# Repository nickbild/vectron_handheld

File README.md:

# Vectron Handheld

Vectron Handheld is a retro handheld gaming console based on the [6502 CPU](https://en.wikipedia.org/wiki/MOS_Technology_6502).  It has five input buttons (up, down, left, right, fire) and a 1.8" 128x160 18-bit color TFT LCD display.  

I have developed an [implementation of Pong](https://github.com/nickbild/vectron_handheld/blob/master/game.asm) to demonstrate Vectron Handheld's capabilities.

## How It Works

The KiCad design files are [available here](https://github.com/nickbild/vectron_handheld/tree/master/vectron_handheld_pcb).

The W65C02 is clocked at 8MHz.  The console has 32KB of RAM, and 32KB of ROM is available to store the game.  A few 7400-series logic chips are used for address decoding and button debouncing.  All components are through-hole, and aside from the modern display, the components are contemporaries of the original 6502 processor.

A W65C22 VIA is used to extend the number of interrupts available to the CPU for capturing button presses.  The VIA is also used to bit bang the SPI TFT LCD display interface.  My implementation of [Pong](https://github.com/nickbild/vectron_handheld/blob/master/game.asm) demonstrates how to use the buttons and the display in a game.

A 273 mm x 221 mm 4-layer PCB was designed in KiCad.  There is definitely opportunity to reduce the size of the board with a tighter layout if a smaller device is desired (this was my first crack at designing a PCB).

The Vectron Handheld runs at 5V and draws ~150 mA of current.

## Media

YouTube:  
https://www.youtube.com/watch?v=bRN5SaRVa04

Vectron Handheld:

Close-up:

The breadboard prototype from which the PCB was designed:

Playing Pong:

Unpopulated PCB:

## Bill of Materials

- 1	x W65C02
- 1	x W65C22
- 1	x 8MHz Crystal
- 1	x SN74HC32N
- 1	x SN74HC08N
- 1	x SN74LS04N
- 2	x 74LS682
- 1	x SN74HC14N
- 1	x AS6C62256A-70PCN
- 1	x AT28C256-15PU
- 6 x pushbutton
- 9	x 10K resistor
- 8	x 3.3K resistor
- 1	x 1.8" 128x160 18-bit color TFT LCD display
- 1	x 220uF capacitor
- 5	x 1,000 pF capacitor
- 2 x 40 pin DIP IC socket
- 2 x 28 pin DIP IC socket

## Also See

Check out some of my other 6502-based projects:

- [Vectron 64 breadboard computer](https://github.com/nickbild/vectron_64)  
- [6502 virtual reality headset](https://github.com/nickbild/vectron_vr)  
- [Play Atari 2600 games with gestures](https://github.com/nickbild/vectron_ai)

## About the Author

[Nick A. Bild, MS](https://nickbild79.firebaseapp.com/#!/)

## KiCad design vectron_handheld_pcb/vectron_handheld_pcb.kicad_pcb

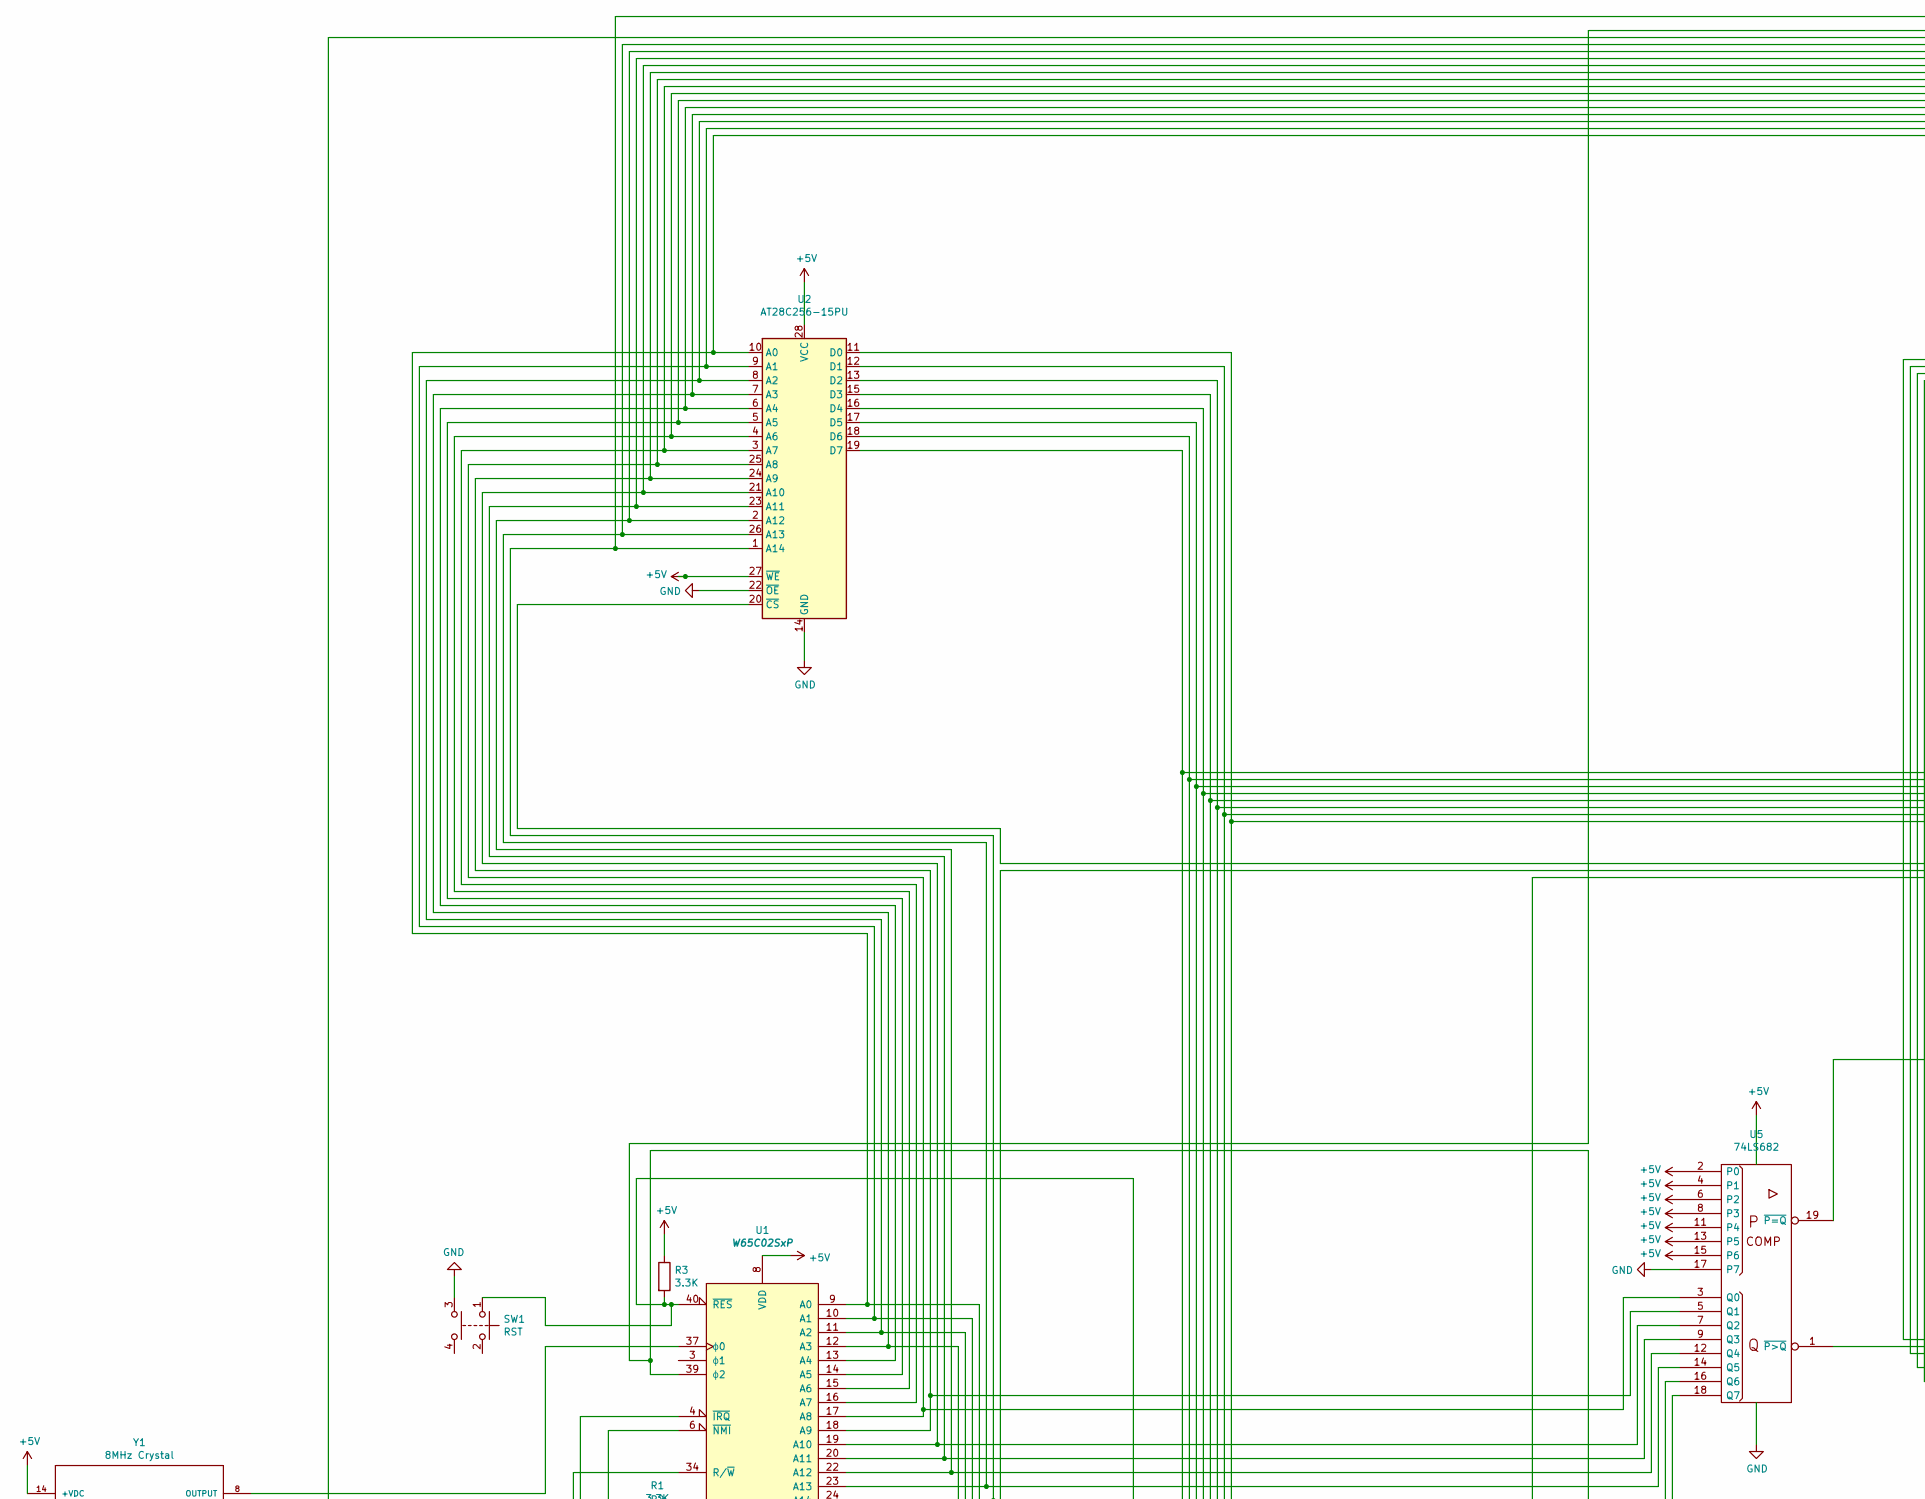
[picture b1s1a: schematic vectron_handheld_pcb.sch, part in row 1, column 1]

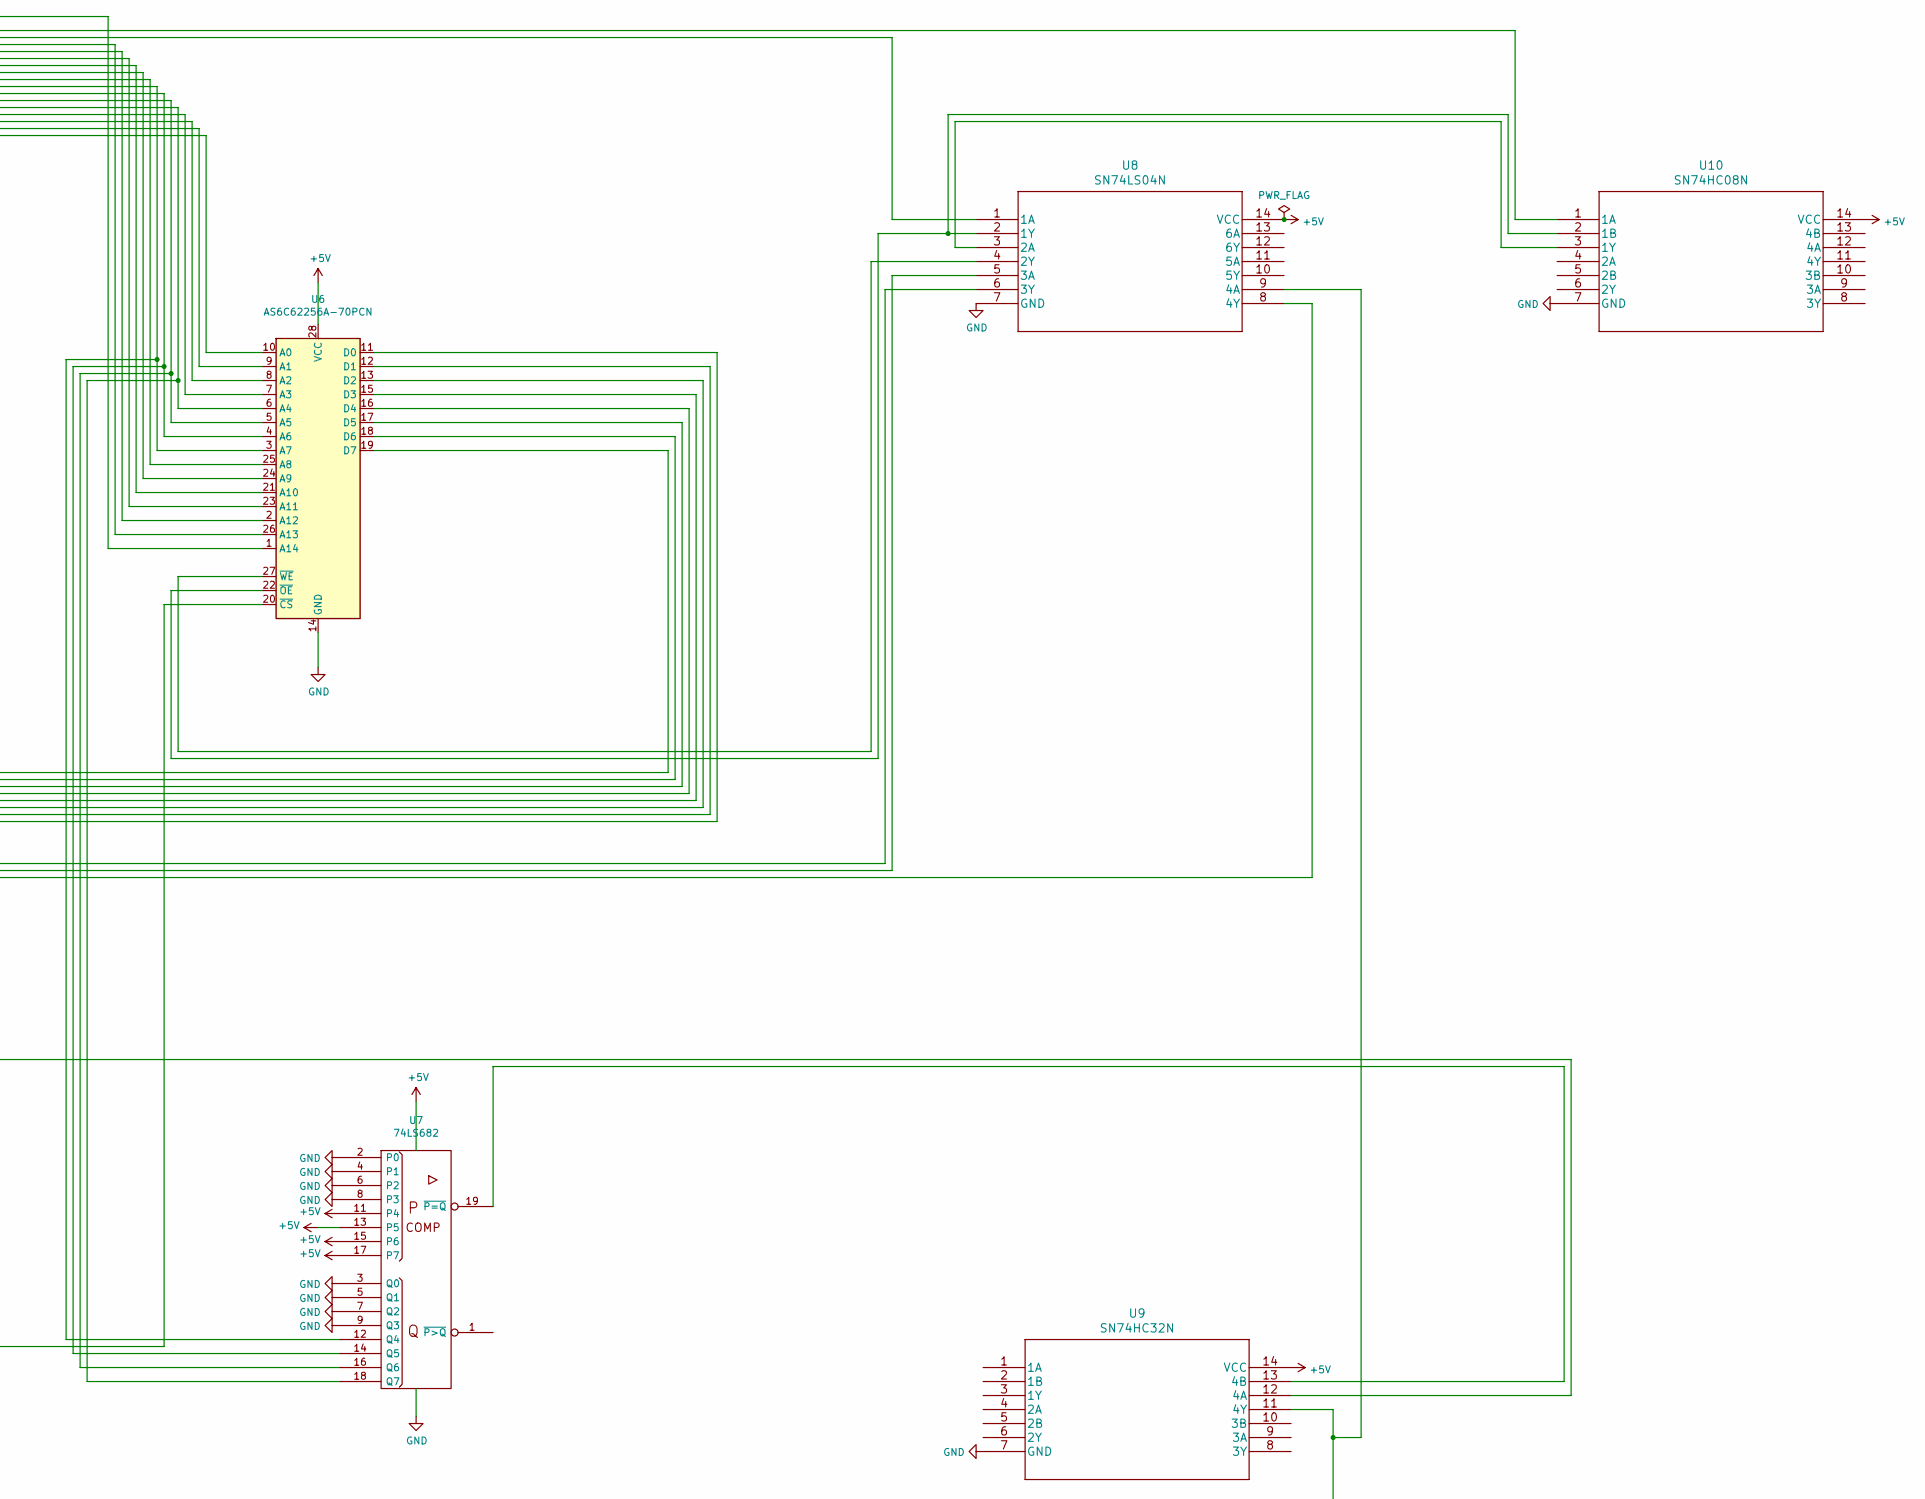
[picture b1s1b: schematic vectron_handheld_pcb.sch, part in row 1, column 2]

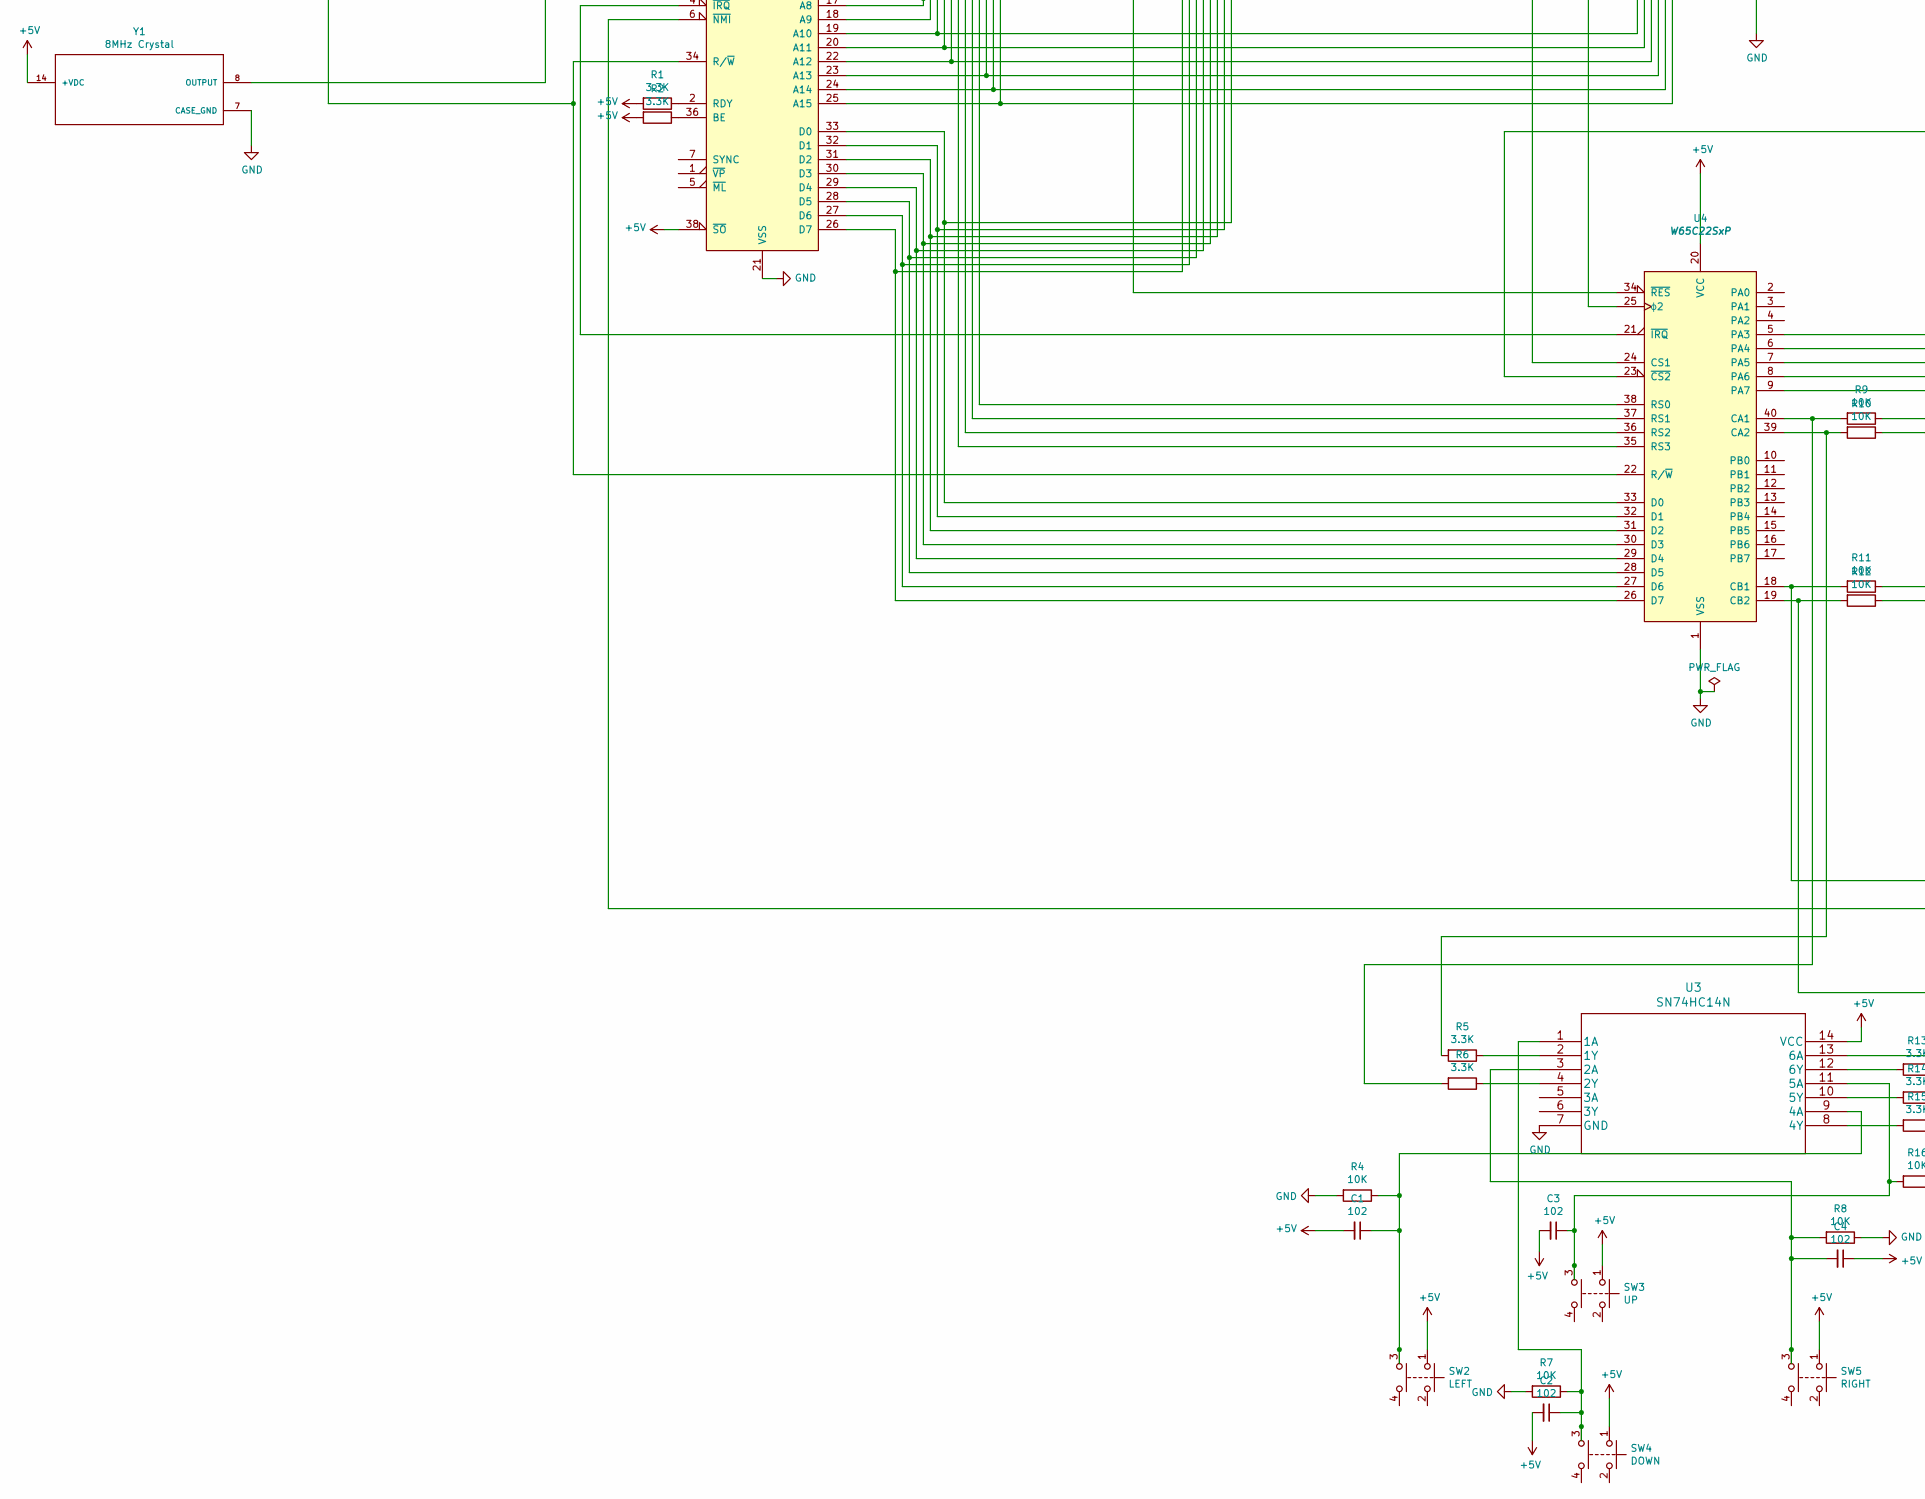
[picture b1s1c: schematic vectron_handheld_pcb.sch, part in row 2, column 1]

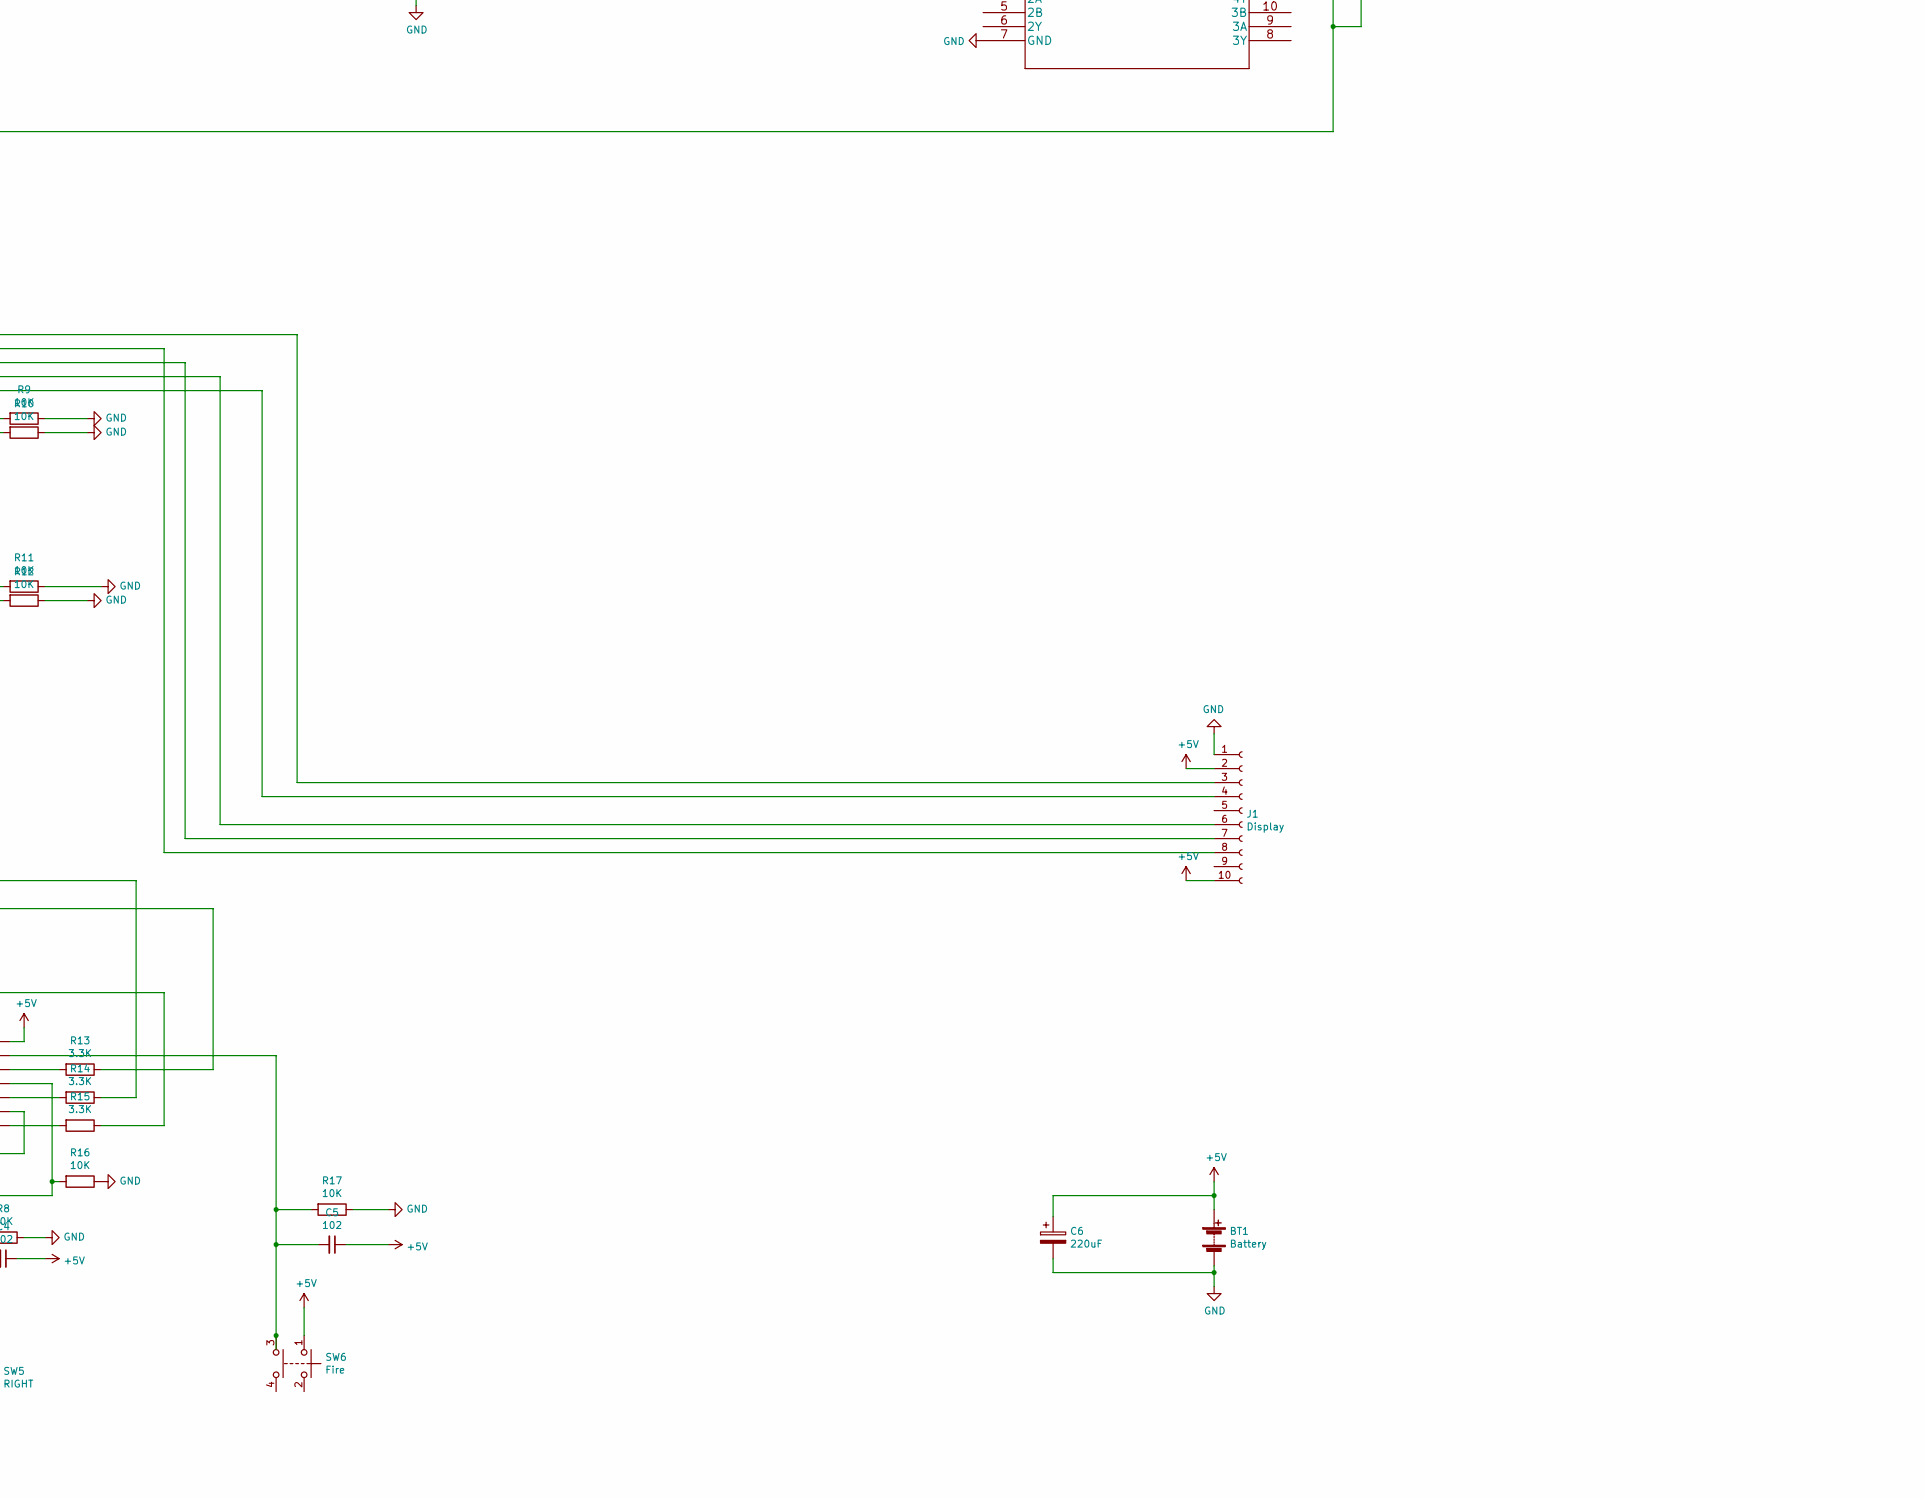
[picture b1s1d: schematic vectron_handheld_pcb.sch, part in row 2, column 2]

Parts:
BT1: Battery; PinHeader_1x02_P2.54mm_Vertical
C1, C2, C3, C4, C5: 102; C_Disc_D5.1mm_W3.2mm_P5.00mm
C6: 220uF; CP_Radial_D8.0mm_P5.00mm
J1: Display; PinHeader_1x10_P2.54mm_Vertical
R1, R2, R3, R5, R6, R13, R14, R15: 3.3K; R_Axial_DIN0207_L6.3mm_D2.5mm_P10.16mm_Horizontal
R4, R7, R8, R9, R10, R11, R12, R16, R17: 10K; R_Axial_DIN0207_L6.3mm_D2.5mm_P10.16mm_Horizontal
SW1: RST; SW_TH_Tactile_Omron_B3F-10xx
SW2: LEFT; SW_TH_Tactile_Omron_B3F-10xx
SW3: UP; SW_TH_Tactile_Omron_B3F-10xx
SW4: DOWN; SW_TH_Tactile_Omron_B3F-10xx
SW5: RIGHT; SW_TH_Tactile_Omron_B3F-10xx
SW6: Fire; SW_TH_Tactile_Omron_B3F-10xx
U1: W65C02SxP; DIP_Socket-40_W11.9_W12.7_W15.24_W17.78_W18.5_3M_240-1280-0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
U2: AT28C256-15PU; DIP_Socket-28_W11.9_W12.7_W15.24_W17.78_W18.5_3M_228-1277-0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
U3: SN74HC14N; DIP_Socket-14_W4.3_W5.08_W7.62_W10.16_W10.9_3M_214-3339-00-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
U4: W65C22SxP; DIP_Socket-40_W11.9_W12.7_W15.24_W17.78_W18.5_3M_240-1280-0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
U5, U7: 74LS682; DIP_Socket-20_W4.3_W5.08_W7.62_W10.16_W10.9_3M_220-3342-00-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
U6: AS6C62256A-70PCN; DIP_Socket-28_W11.9_W12.7_W15.24_W17.78_W18.5_3M_228-1277-0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
U8: SN74LS04N; DIP_Socket-14_W4.3_W5.08_W7.62_W10.16_W10.9_3M_214-3339-00-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
U9: SN74HC32N; DIP_Socket-14_W4.3_W5.08_W7.62_W10.16_W10.9_3M_214-3339-00-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
U10: SN74HC08N; DIP_Socket-14_W4.3_W5.08_W7.62_W10.16_W10.9_3M_214-3339-00-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
Y1: 8MHz Crystal; Oscillator_DIP-14

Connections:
+5V: BT1.1 (+), C1.2, C2.2, C3.2, C4.1, C5.1, C6.1, J1.2, J1.10, R1.2, R2.2, R3.1, SW2.1, SW3.1, SW4.1, SW5.1, SW6.1, U1.8 (VDD), U1.38 (~SO), U2.27 (~WE), U2.28 (VCC), U3.14 (VCC), U4.20 (VCC), U5.2 (P0), U5.4 (P1), U5.6 (P2), U5.8 (P3), U5.11 (P4), U5.13 (P5), U5.15 (P6), U5.20 (Vcc), U6.28 (VCC), U7.11 (P4), U7.13 (P5), U7.15 (P6), U7.17 (P7), U7.20 (Vcc), U8.14 (VCC), U9.14 (VCC), U10.14 (VCC), Y1.14 (+VDC)
GND: BT1.2 (-), C6.2, J1.1, R4.2, R7.2, R8.1, R9.1, R10.1, R11.1, R12.1, R16.1, R17.1, SW1.3, U1.21 (VSS), U2.14 (GND), U2.22 (~OE), U3.7 (GND), U4.1 (VSS), U5.10 (Gnd), U5.17 (P7), U6.14 (GND), U7.2 (P0), U7.3 (Q0), U7.4 (P1), U7.5 (Q1), U7.6 (P2), U7.7 (Q2), U7.8 (P3), U7.9 (Q3), U7.10 (Gnd), U8.7 (GND), U9.7 (GND), U10.7 (GND), Y1.7 (CASE_GND)
unnamed: C1.1, R4.1, SW2.3, U3.9 (4A)
unnamed: C2.1, R7.1, SW4.3, U3.1 (1A)
unnamed: C3.1, R16.2, SW3.3, U3.11 (5A)
unnamed: C4.2, R8.2, SW5.3, U3.3 (2A)
unnamed: C5.2, R17.2, SW6.3, U3.13 (6A)
unnamed: J1.3, U4.5 (PA3)
unnamed: J1.4, U4.9 (PA7)
unnamed: J1.6, U4.8 (PA6)
unnamed: J1.7, U4.7 (PA5)
unnamed: J1.8, U4.6 (PA4)
unnamed: R1.1, U1.2 (RDY)
unnamed: R2.1, U1.36 (BE)
unnamed: R3.2, SW1.1, U1.40 (~RES), U4.34 (~RES)
unnamed: R5.1, U3.2 (1Y)
unnamed: R6.1, U3.4 (2Y)
unnamed: R6.2, R9.2, U4.40 (CA1)
unnamed: R5.2, R10.2, U4.39 (CA2)
unnamed: R11.2, R14.1, U4.18 (CB1)
unnamed: R12.2, R15.1, U4.19 (CB2)
unnamed: R13.1, U1.6 (~NMI)
unnamed: R13.2, U3.12 (6Y)
unnamed: R14.2, U3.10 (5Y)
unnamed: R15.2, U3.8 (4Y)
unnamed: U1.4 (~IRQ), U4.21 (~IRQ)
unnamed: U1.9 (A0), U2.10 (A0), U4.38 (RS0), U6.10 (A0)
unnamed: U1.10 (A1), U2.9 (A1), U4.37 (RS1), U6.9 (A1)
unnamed: U1.11 (A2), U2.8 (A2), U4.36 (RS2), U6.8 (A2)
unnamed: U1.12 (A3), U2.7 (A3), U4.35 (RS3), U6.7 (A3)
unnamed: U1.13 (A4), U2.6 (A4), U6.6 (A4), U7.18 (Q7)
unnamed: U1.14 (A5), U2.5 (A5), U6.5 (A5), U7.16 (Q6)
unnamed: U1.15 (A6), U2.4 (A6), U6.4 (A6), U7.14 (Q5)
unnamed: U1.16 (A7), U2.3 (A7), U6.3 (A7), U7.12 (Q4)
unnamed: U1.17 (A8), U2.25 (A8), U5.3 (Q0), U6.25 (A8)
unnamed: U1.18 (A9), U2.24 (A9), U5.5 (Q1), U6.24 (A9)
unnamed: U1.19 (A10), U2.21 (A10), U5.7 (Q2), U6.21 (A10)
unnamed: U1.20 (A11), U2.23 (A11), U5.9 (Q3), U6.23 (A11)
unnamed: U1.22 (A12), U2.2 (A12), U5.12 (Q4), U6.2 (A12)
unnamed: U1.23 (A13), U2.26 (A13), U5.14 (Q5), U6.26 (A13)
unnamed: U1.24 (A14), U2.1 (A14), U5.16 (Q6), U6.1 (A14)
unnamed: U1.25 (A15), U5.18 (Q7), U8.5 (3A)
unnamed: U1.26 (D7), U2.19 (D7), U4.26 (D7), U6.19 (D7)
unnamed: U1.27 (D6), U2.18 (D6), U4.27 (D6), U6.18 (D6)
unnamed: U1.28 (D5), U2.17 (D5), U4.28 (D5), U6.17 (D5)
unnamed: U1.29 (D4), U2.16 (D4), U4.29 (D4), U6.16 (D4)
unnamed: U1.30 (D3), U2.15 (D3), U4.30 (D3), U6.15 (D3)
unnamed: U1.31 (D2), U2.13 (D2), U4.31 (D2), U6.13 (D2)
unnamed: U1.32 (D1), U2.12 (D1), U4.32 (D1), U6.12 (D1)
unnamed: U1.33 (D0), U2.11 (D0), U4.33 (D0), U6.11 (D0)
unnamed: U1.34 (R/~W), U4.22 (R/~W), U8.1 (1A)
unnamed: U1.37 (ϕ0), Y1.8 (OUTPUT)
unnamed: U1.39 (ϕ2), U4.25 (ϕ2), U10.1 (1A)
unnamed: U2.20 (~CS), U8.6 (3Y)
unnamed: U4.23 (~CS2), U8.9 (4A), U9.11 (4Y)
unnamed: U4.24 (CS1), U8.8 (4Y)
unnamed: U5.1 (~P>Q), U6.20 (~CS)
unnamed: U5.19 (~P=Q), U9.12 (4A)
unnamed: U6.27 (~WE), U8.4 (2Y)
unnamed: U7.19 (~P=Q), U9.13 (4B)
unnamed: U6.22 (~OE), U8.2 (1Y), U10.2 (1B)
unnamed: U8.3 (2A), U10.3 (1Y)

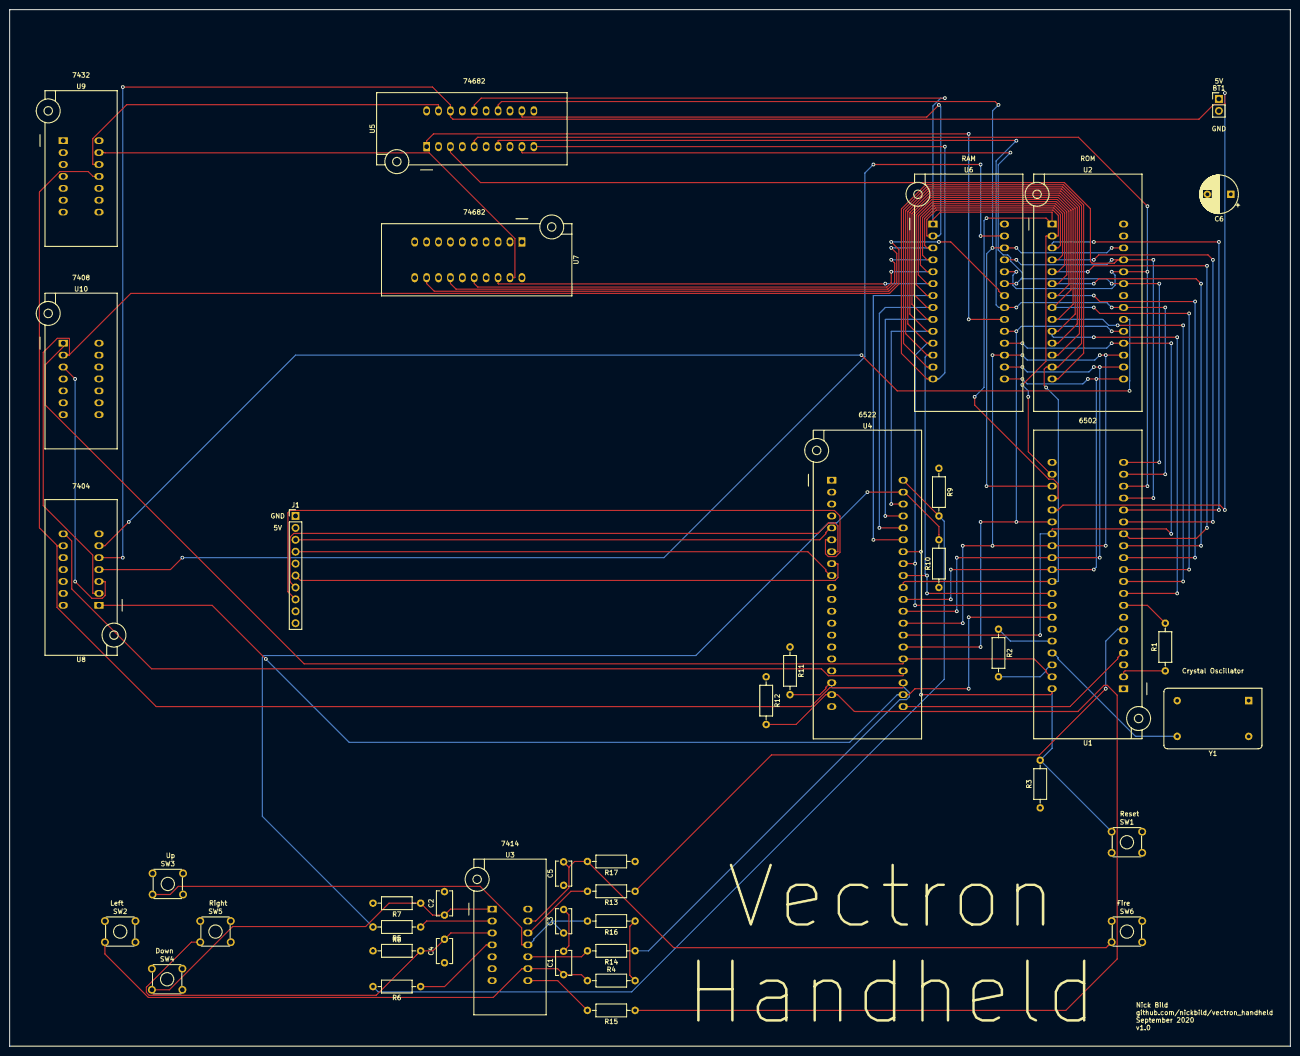
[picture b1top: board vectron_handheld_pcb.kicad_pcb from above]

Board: 4 copper layers, 273.1 x 221.0 mm, 42 parts (0 on the bottom side), 62 nets.

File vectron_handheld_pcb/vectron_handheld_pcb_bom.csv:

"Id";"Designator";"Package";"Quantity";"Designation";"Supplier and ref";
1;"U9";"DIP_Socket-14_W4.3_W5.08_W7.62_W10.16_W10.9_3M_214-3339-00-0602J";1;"SN74HC32N";;;
2;"Y1";"Oscillator_DIP-14";1;"8MHz Crystal";;;
3;"U10";"DIP_Socket-14_W4.3_W5.08_W7.62_W10.16_W10.9_3M_214-3339-00-0602J";1;"SN74HC08N";;;
4;"U8";"DIP_Socket-14_W4.3_W5.08_W7.62_W10.16_W10.9_3M_214-3339-00-0602J";1;"SN74LS04N";;;
5;"U7,U5";"DIP_Socket-20_W4.3_W5.08_W7.62_W10.16_W10.9_3M_220-3342-00-0602J";2;"74LS682";;;
6;"U6";"DIP_Socket-28_W11.9_W12.7_W15.24_W17.78_W18.5_3M_228-1277-00-0602J";1;"AS6C62256A-70PCN";;;
7;"U4";"DIP_Socket-40_W11.9_W12.7_W15.24_W17.78_W18.5_3M_240-1280-00-0602J";1;"W65C22SxP";;;
8;"U3";"DIP_Socket-14_W4.3_W5.08_W7.62_W10.16_W10.9_3M_214-3339-00-0602J";1;"SN74HC14N";;;
9;"U2";"DIP_Socket-28_W11.9_W12.7_W15.24_W17.78_W18.5_3M_228-1277-00-0602J";1;"AT28C256-15PU";;;
10;"U1";"DIP_Socket-40_W11.9_W12.7_W15.24_W17.78_W18.5_3M_240-1280-00-0602J";1;"W65C02SxP";;;
11;"SW6";"SW_TH_Tactile_Omron_B3F-10xx";1;"Fire";;;
12;"SW5";"SW_TH_Tactile_Omron_B3F-10xx";1;"RIGHT";;;
13;"SW4";"SW_TH_Tactile_Omron_B3F-10xx";1;"DOWN";;;
14;"SW3";"SW_TH_Tactile_Omron_B3F-10xx";1;"UP";;;
15;"SW2";"SW_TH_Tactile_Omron_B3F-10xx";1;"LEFT";;;
16;"SW1";"SW_TH_Tactile_Omron_B3F-10xx";1;"RST";;;
17;"R17,R16,R12,R11,R10,R9,R8,R7,R4";"R_Axial_DIN0207_L6.3mm_D2.5mm_P10.16mm_Horizontal";9;"10K";;;
18;"R15,R14,R13,R6,R5,R3,R2,R1";"R_Axial_DIN0207_L6.3mm_D2.5mm_P10.16mm_Horizontal";8;"3.3K";;;
19;"J1";"PinHeader_1x10_P2.54mm_Vertical";1;"Display";;;
20;"C6";"CP_Radial_D8.0mm_P5.00mm";1;"220uF";;;
21;"C5,C4,C3,C2,C1";"C_Disc_D5.1mm_W3.2mm_P5.00mm";5;"102";;;
22;"BT1";"PinHeader_1x02_P2.54mm_Vertical";1;"Battery";;;

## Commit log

2020-08-28 Initial commit.
2020-09-02 Add display init code.
2020-09-03 Display working.
2020-09-03 Exclude files.
2020-09-03 Screen clear working.
2020-09-03 All 5 interrupts and display tested/working.
2020-09-04 Update documentation.
2020-09-16 Draw background.
2020-09-19 Optimize rectangle drawing.
2020-09-19 Add player paddle.
2020-09-20 Player paddle working.
2020-09-20 Add basic ball movement.
2020-09-20 Add ball bouncing physics for screen edges.
2020-09-21 Point scoring logic added.
2020-09-21 Fix paddle1 boundaries and net redraw.
2020-09-22 Computer player AI working.
2020-09-22 Fix pixel offset issue with ball-paddle collision.
2020-09-23 Start KiCad schematics.
2020-09-24 Add updated image.
2020-09-24 Save progress.
2020-09-25 Schematic finished.
2020-09-25 Begin PCB layout.
2020-09-26 Save PCB layout.
2020-09-26 Finished routing.
2020-09-26 Resize board..
2020-09-26 Add silk screen labels.
2020-10-08 Add gerber files and BOM.
2020-10-08 Clean up.
